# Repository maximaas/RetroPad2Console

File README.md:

# RetroPad2Console

for SNES & Saturn pads using on original xbox and gamecube.

Copyright (C) 2015,2017 Maximaas<br/>
Version 1.0 - completed on 2015.12.09

<H2>About</H2>
Original Xbox and Nintendo Gamecube(Europe version) are good emulator platforms with RGB video support, which makes it possible to play retro games on a RGB capable CRT display. But with weird controller scheme, the default Xbox and GC controller are disasters for most retro games. So I came up with the idea of making an adapter to let me use SNES and Saturn pads on these consoles. Saturn pad has six buttons on the right, it's perfect for MegaDrive and 2D-Fighting games while SNES pad is for NES/SNES/GBP and other games.

<H2>References</H2>
Before I start, I googled a lot of resources to help me accomplish this project (see blow). Greate thanks to all these authors.<br/><br/>

http://www.int03.co.uk/crema/hardware/gamecube/gc-control.htm<br/>
Gamecube controlle protocol explanation.

http://www.raphnet.net/electronique/x2wii/index_en.php<br/>
N64/Snes/Nes controller to gamecube/Wii conversion project

https://github.com/brownan/Gamecube-N64-Controller<br/>
I directly used the gamecube communication code from this project with just a little modification. It helps me greatly, without this I will never done my work.

http://www.brunofreitas.com/node/41<br/>
https://github.com/bootsector/usb-retropad-adapter<br/>
A very powerful adapter, I directly used the Xbox pad communication code from this project or I will never got my project work on original xbox.

<H2>Pictures</H2>

<br/>
I bought several SNES to PC adapters to make use of its case and snes female connector.

<br/>
My work uses USB connector as the output in order to adapt both Xbox and GC.

<br/>
Interface cable. Female USB connector to Xbox and GC controller port.

<br/>
The PCB I designed with the size fits with the SNES to PC adapter case. And a bit of hand craft work should be done to accommodate the Saturn and USB connectors.

<H2>Parts</H2>

| Parts    | Model          | Remark                 |
|:---------|:---------------|:-----------------------|
| MCU      | ATMEGA8-16PU   | Can be replaced with ATMEGA328p for more program memory                       |
| CRYSTAL  | 16 MHz         |                        |
| R_RST    | 120 Ohm        |                        |
| R_LED    | 220 Ohm        |                        |
| R_USB    | 1.5K Ohm       |                        |
| R_D+     | 68 Ohm         |                        |
| R_D-     | 68 Ohm         |                        |
| C1       | 22 pf          |                        |
| C2       | 22 pf          |                        |
| C3       | 4.7 uf         |                        |
| D1       | 1N4148         |                        |
| D2       | 1N4148         |                        |
| SWITCH   | Reset Switch   |                        |
| LED      | Any 5v LED     |                        |
| USB-A    | /              | USB-A Male connector   |
| SFC      | /              | SFC conenctor          |
| SS       | /              | SS connector           |
|          |                |                        |
| GC Cable | /              | NGC extesion cable     |
| XB Cable | /              | XBOX extension cable   |
| USB      | /              | USB-A female connector |

<H2>Build the Adapter</H2>
This adapter is actually a minimum Arduino based on ATMEGA8-16PU. It receives the SNES/Saturn pad signals then interprete and send them to the target according to Xbox or GC protocol.

The eagle files of the hardware part are included. The PCB have both ICSP and Serial interfaces on it, for bootloader and firmware programming.

The software part is standard Arduino sketch codes, can be compiled and uploaded with Arduino IDE.

With the parts assembled, upload the "optiboot_atmega8" bootloader by ICSP which can be found in Arduino IDE releases. 

The firmware can be uploaded by either ICSP or Serial interface. For Serial way, the reset button need to be hit right after you clicked the upload button in Arduino IDE.

BTW, I'm using Sloeber IDE(http://eclipse.baeyens.it/) to help keeping my Arduino projects well organized.

<H2>Interface cable wiring</H2>

Here's a picture of male usb connector, I named the 4 pins to U1/U2/U3/U4, then wired them to the consoles' controller port.

<ul>
<li>Xbox</li>
</ul>
The adapter uses the standard usb pinout and V-USB library to communicate with Xbox which makes the wiring things very simple.

Just follow the image above.

<ul>
<li>Gamecube</li>
</ul>
Gamecube only have one data line to carry the signal which connected to PD2(D+ pin) in my case.

It is the view of the controller port on Gamecube.<br/>
pin1   --> U1<br/>
pin2   --> U3<br/>
pin4&5 --> U4<br/>
The D- line is left empty.<br/>

<H2>Known Issues</H2>
<ul>
<li>The turning on of the LED on the adapter means the handshaking process is over and the adapter is funtional. Unlike the Gamecube, the Xbox will not do the handshaking process with the controller until the power on video clip is finished. When cold-plugged to the Xbox the adapter will be funtional after the console started.</li>
<br/>
<li>The adapter can not work with Game Boy Interface (a replacement to the official Gameboy Player application) because of a different handshaking protocol. The ATMEGA8-16PU only have 8KB memory, adding any fix codes will cause it reachs it's physical limit.</li>
</ul>

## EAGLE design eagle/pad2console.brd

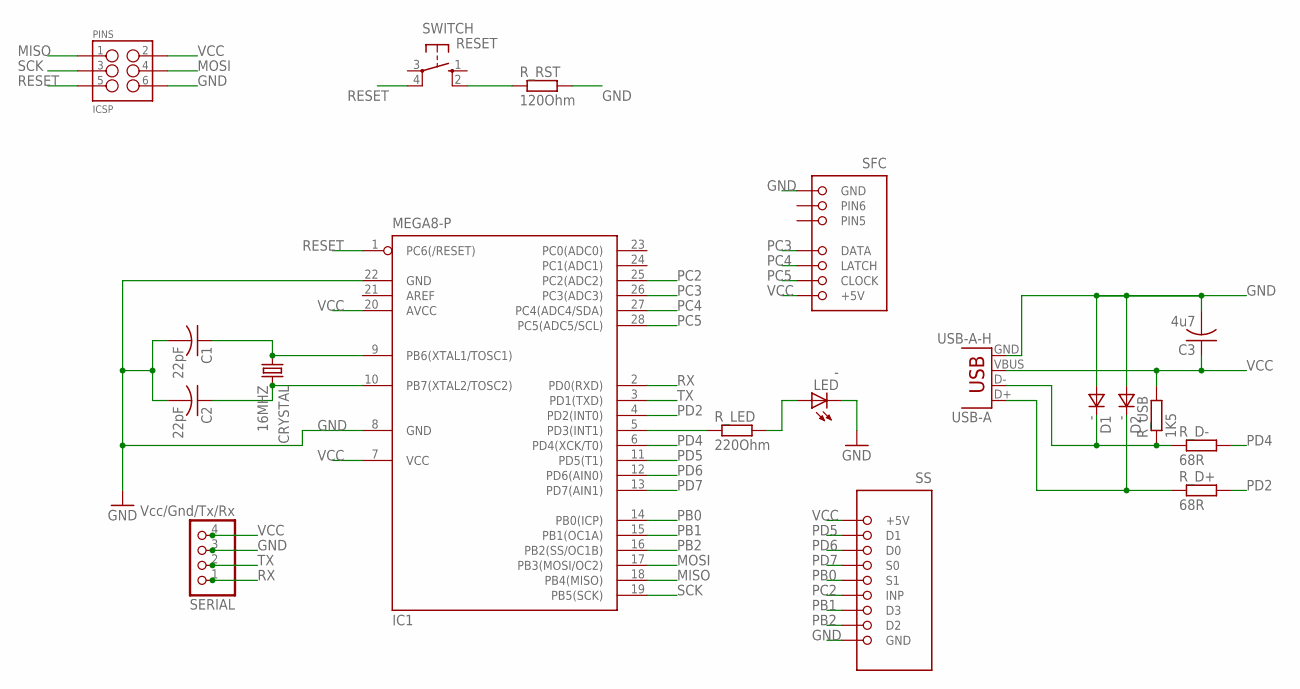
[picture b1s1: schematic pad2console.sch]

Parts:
C1, C2: 22pF; C050-024X044
C3: 4u7; C050-024X044
CRYSTAL: 16MHZ; HC49/S
D1, D2: -; E2LINE
IC1: MEGA8-P; DIL28-3
LED: -; LD260
PINS: ICSP; 2X3-SHROUDED
R_D+: 68R; 0204/5
R_D-: 68R; 0204/5
R_LED: 220Ohm; 0204/5
R_RST: 120Ohm; 0204/5
R_USB: 1K5; 0204/5
SERIAL: Vcc/Gnd/Tx/Rx; 1X04
SFC: SFC_PIN
SS: SS_PIN
SWITCH: RESET; B3F-10XX
USB-A: USB-A-H

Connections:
D+: D2.1 (C), R_D+.1, USB-A.D+
D-: D1.1 (C), R_D-.1, R_USB.1, USB-A.D-
GND: C1.2, C2.2, C3.2, D1.2 (A), D2.2 (A), IC1.8 (GND), IC1.22 (GND), LED.K (C), PINS.6, R_RST.2, SERIAL.3, SFC.PIN7 (GND), SS.PIN9 (GND), USB-A.GND
MISO: IC1.18 (PB4(MISO)), PINS.1
MOSI: IC1.17 (PB3(MOSI/OC2)), PINS.4
unnamed: LED.A, R_LED.2
unnamed: R_RST.1, SWITCH.2 (S1)
PB0: IC1.14 (PB0(ICP)), SS.PIN5 (S1)
PB1: IC1.15 (PB1(OC1A)), SS.PIN7 (D3)
PB2: IC1.16 (PB2(SS/OC1B)), SS.PIN8 (D2)
PB6: C1.1, CRYSTAL.1, IC1.9 (PB6(XTAL1/TOSC1))
PB7: C2.1, CRYSTAL.2, IC1.10 (PB7(XTAL2/TOSC2))
PC2: IC1.25 (PC2(ADC2)), SS.PIN6 (INP)
PC3: IC1.26 (PC3(ADC3)), SFC.PIN4 (DATA)
PC4: IC1.27 (PC4(ADC4/SDA)), SFC.PIN3 (LATCH)
PC5: IC1.28 (PC5(ADC5/SCL)), SFC.PIN2 (CLOCK)
PD2: IC1.4 (PD2(INT0)), R_D+.2
PD3: IC1.5 (PD3(INT1)), R_LED.1
PD4: IC1.6 (PD4(XCK/T0)), R_D-.2
PD5: IC1.11 (PD5(T1)), SS.PIN2 (D1)
PD6: IC1.12 (PD6(AIN0)), SS.PIN3 (D0)
PD7: IC1.13 (PD7(AIN1)), SS.PIN4 (S0)
RESET: IC1.1 (PC6(/RESET)), PINS.5, SWITCH.4 (P1)
RX: IC1.2 (PD0(RXD)), SERIAL.1
SCK: IC1.19 (PB5(SCK)), PINS.3
TX: IC1.3 (PD1(TXD)), SERIAL.2
VCC: C3.1, IC1.7 (VCC), IC1.20 (AVCC), PINS.2, R_USB.2, SERIAL.4, SFC.PIN1 (+5V), SS.PIN1 (+5V), USB-A.VBUS

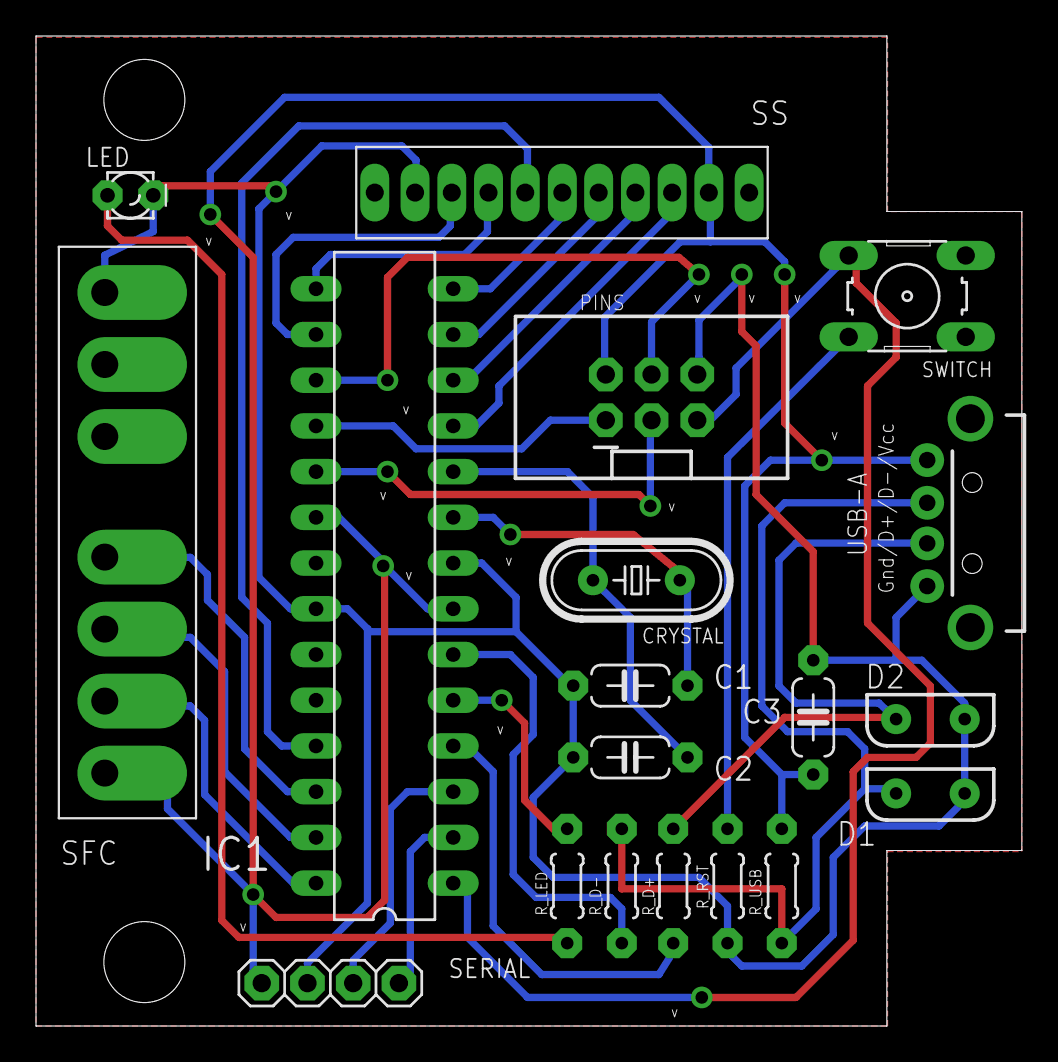
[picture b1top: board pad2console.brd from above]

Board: 2 copper layers, 54.8 x 55.0 mm, 19 parts (0 on the bottom side), 27 nets.

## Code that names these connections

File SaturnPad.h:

/**
 * Saturn pad buttons events
 *
 * Copyright (C) 2015,2017 Maximaas
 * Version 1.0 - completed on 2015.12.09
 * Contact: mingzo@gmail.com
 */
#ifndef SaturnPad_h
#define SaturnPad_h

#include "Arduino.h"

#include <inttypes.h>

/**
 * Saturn controller pinout
 *
 * 1   2   3   4   5   6   7   8   9
 * VCC D1  D0  S0  S1  5v  D3  D2  GND
 * VCC PD5 PD6 PD7 PB0 PC2 PB1 PB2 GND
 */

#define PIN_SATURN_D0  6  //PD6, ss pad pin3
#define PIN_SATURN_D1  5  //PD5, ss pad pin2
#define PIN_SATURN_D2 10  //PB2, ss pad pin8
#define PIN_SATURN_D3  9  //PB1, ss pad pin7
#define PIN_SATURN_S0  7  //PD7, ss pad pin4
#define PIN_SATURN_S1  8  //PB0, ss pad pin5


#define SATURN_Z      B00001000 //0x08  8
#define SATURN_Y      B00000100 //0x04  4
#define SATURN_X      B00000010 //0x02  2
#define SATURN_R      B00000001 //0x01  1

#define SATURN_B      B00001000
#define SATURN_C      B00000100
#define SATURN_A      B00000010
#define SATURN_START  B00000001

#define SATURN_UP     B00001000
#define SATURN_DOWN   B00000100
#define SATURN_LEFT   B00000010
#define SATURN_RIGHT  B00000001

#define SATURN_L      B00001101

class SaturnPad {

  public:
	int connected;

	SaturnPad();
    void init();
    void wait();
    int* buttons();

  private:

};

#endif

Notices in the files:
parts and their libraries:
SparkFun-Connectors: Licensing: CC v3.0 Share-Alike You are welcome to use this library for commercial purposes.
SparkFun-Aesthetics: Licensing: Creative Commons ShareAlike 4.0 International - https://creativecommons.org/licenses/by-sa/4.0
